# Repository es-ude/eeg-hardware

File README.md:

# 8-Channel EEG System

This repository contains the complete design and source files for a custom **8-Channel EEG System** (Electroencephalography) based on the Raspberry Pi Pico (RP2350A) and the Analog Devices AD7779 24-bit ADC.

The project is modular and covers the entire signal chain: from physical schematics and microcontroller firmware to data acquisition and visualization on the PC.

## Project Structure

The repository is organized into three main sections:

- **[`0_hardware/`](0_hardware/)**: KiCad projects for schematics and PCB layouts.
- **[`1_firmware/`](1_firmware/)**: C source code to be flashed onto the hardware.
- **[`2_pc_datahandler/`](2_pc_datahandler/)**: Python framework for control, data acquisition (LSL/HDF5), live plotting, and analysis.

---

## 0_Hardware

The hardware folder contains all electronic design files (KiCad).

**Key Components:**
*   **MCU:** Custom desgin based on the **RP2350A**.
*   **ADC:** [AD7779](https://www.analog.com/en/products/ad7779.html) (8-Channel, 24-Bit Sigma-Delta ADC).
*   **Signal Conditioning:** Variable gain settings via digital potentiometers (AD5142A).
*   **Modules:** Separate schematics for power management, impedance measurement, sensor interfaces, and active shielding reference.

---

## 1_Firmware

The firmware runs on the RP2350A and handles SPI communication with the ADC, I2C communication with digital potentiometers, and high-speed data transfer to the PC via USB.

**Features:**
*   **Sampling Rate:** Configurable sampling rate for the AD7779.
*   **Drivers:** Implemented for AD7779 (SPI), AD5142A (I2C), and GPIO shielding control.
*   **Protocol:** USB packet protocol with header/footer framing.
*   **Synchronization:** Microsecond-precision timestamping for every data packet.

**Build Instructions:**
Prerequisites: [Pico SDK](https://github.com/raspberrypi/pico-sdk) and CMake.

---

## 2_PC_DataHandler

This folder contains the Python-based host software to interface with the EEG hardware. It manages the USB connection, decodes the raw data stream, and integrates with the Lab Streaming Layer (LSL) ecosystem.

**Features:**
*   **Data Acquisition:** Reading from the USB serial port.
*   **LSL Integration:** Streams data as an 8-channel EEG signal onto the local network for use with tools like LabRecorder or our live plotter.
*   **Visualization:** Real-time plotting of time-series data.
*   **Analysis:** Signal quality verification.

**This project uses [`uv`](https://github.com/astral-sh/uv) for fast and reliable dependency management.**

Create a virtual environment and sync dependencies:
    ```bash
    uv sync
    ```

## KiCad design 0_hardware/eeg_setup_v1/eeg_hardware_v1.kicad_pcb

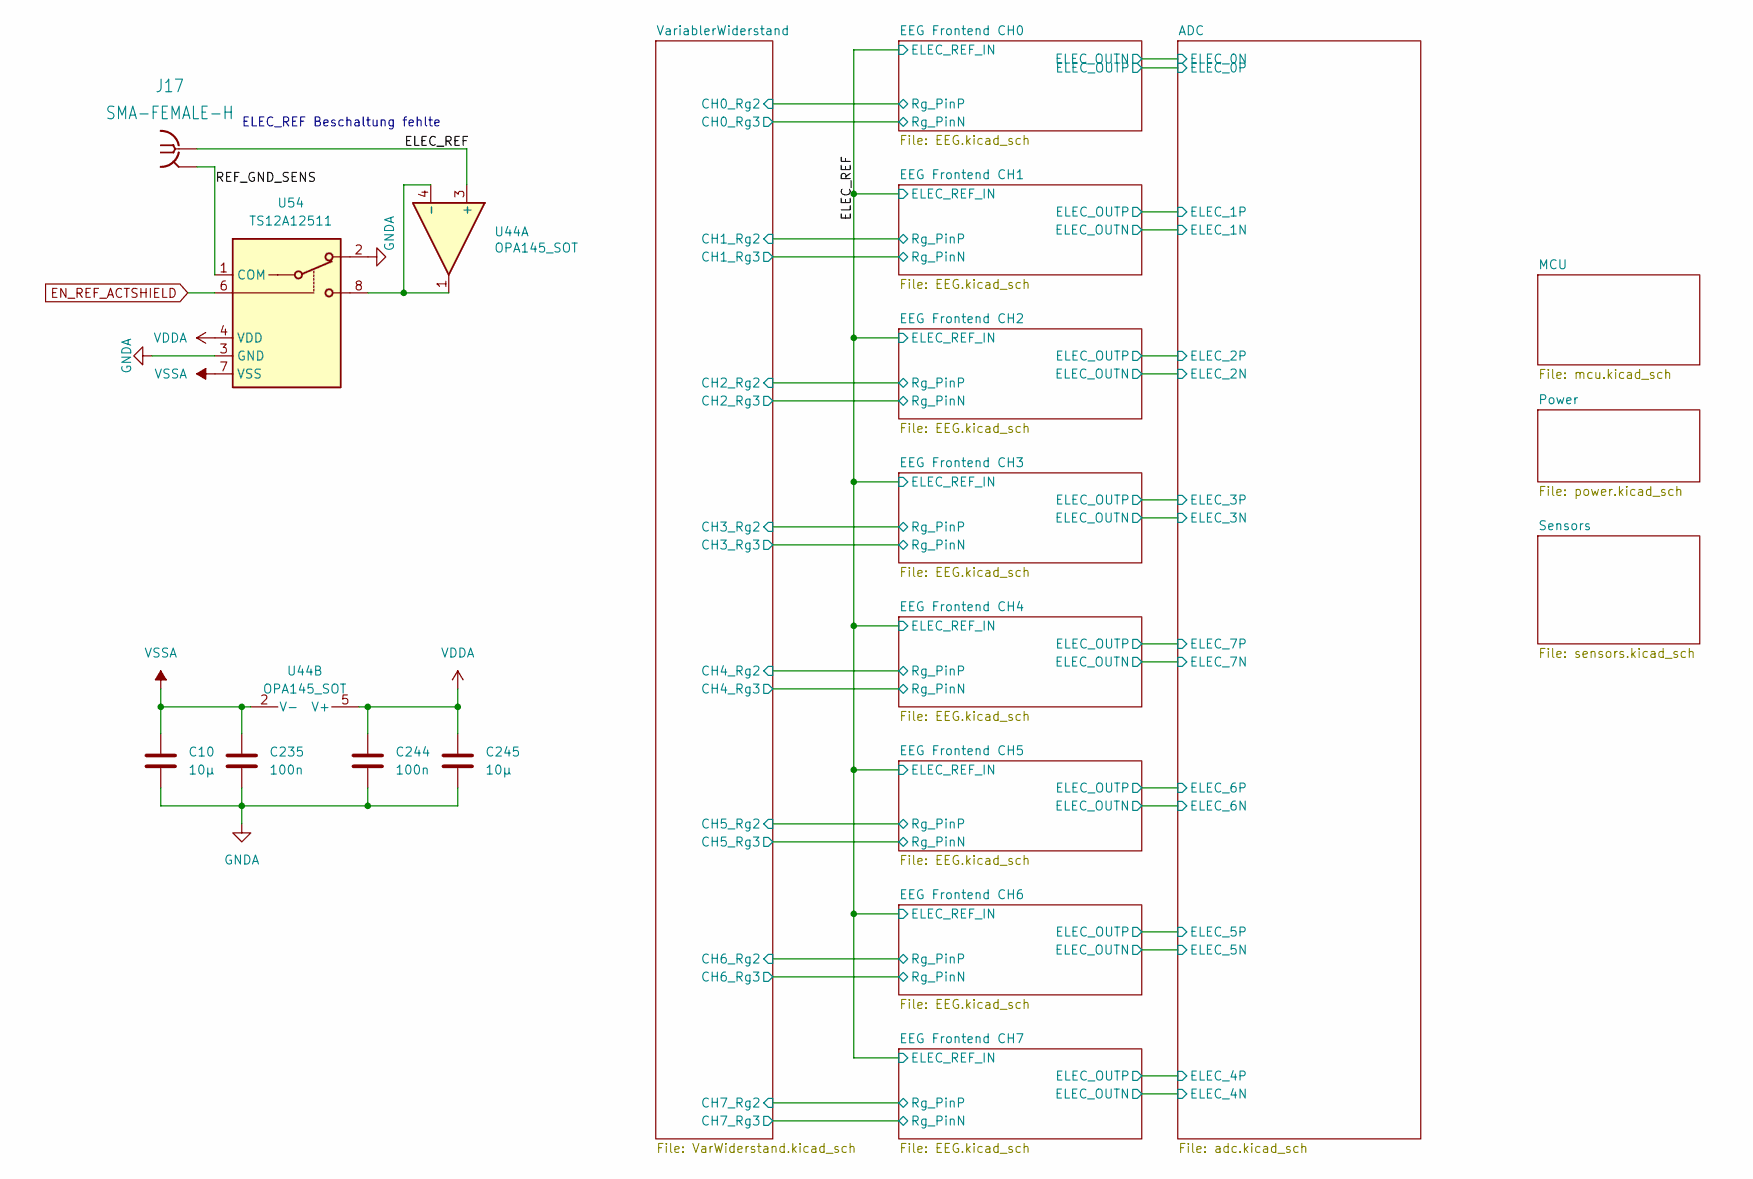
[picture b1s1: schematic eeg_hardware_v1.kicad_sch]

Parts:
C10, C245: 10µ; C_0603_1608Metric
C235, C244: 100n; C_0603_1608Metric
J17: SMA-FEMALE-H; SMA_Samtec_SMA-J-P-H-ST-EM1_EdgeMount
U44: OPA145_SOT; SOT-23-5_HandSoldering
U54: TS12A12511; SOT-23-8

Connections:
/ELEC_REF: J17.1 (SIG), U44.3 (+); also elsewhere on the board
/REF_GND_SENS: J17.2 (GND), U54.1 (COM)
EN_REF_ACTSHIELD: U54.6; also elsewhere on the board
GNDA: C10.2, C235.2, C244.2, C245.2, U54.2, U54.3 (GND); also elsewhere on the board
unnamed: U44.1, U44.4 (-), U54.8
VDDA: C244.1, C245.1, U44.5 (V+), U54.4 (VDD); also elsewhere on the board
VSSA: C10.1, C235.1, U44.2 (V-), U54.7 (VSS); also elsewhere on the board

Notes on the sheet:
ELEC_REF Beschaltung fehlte

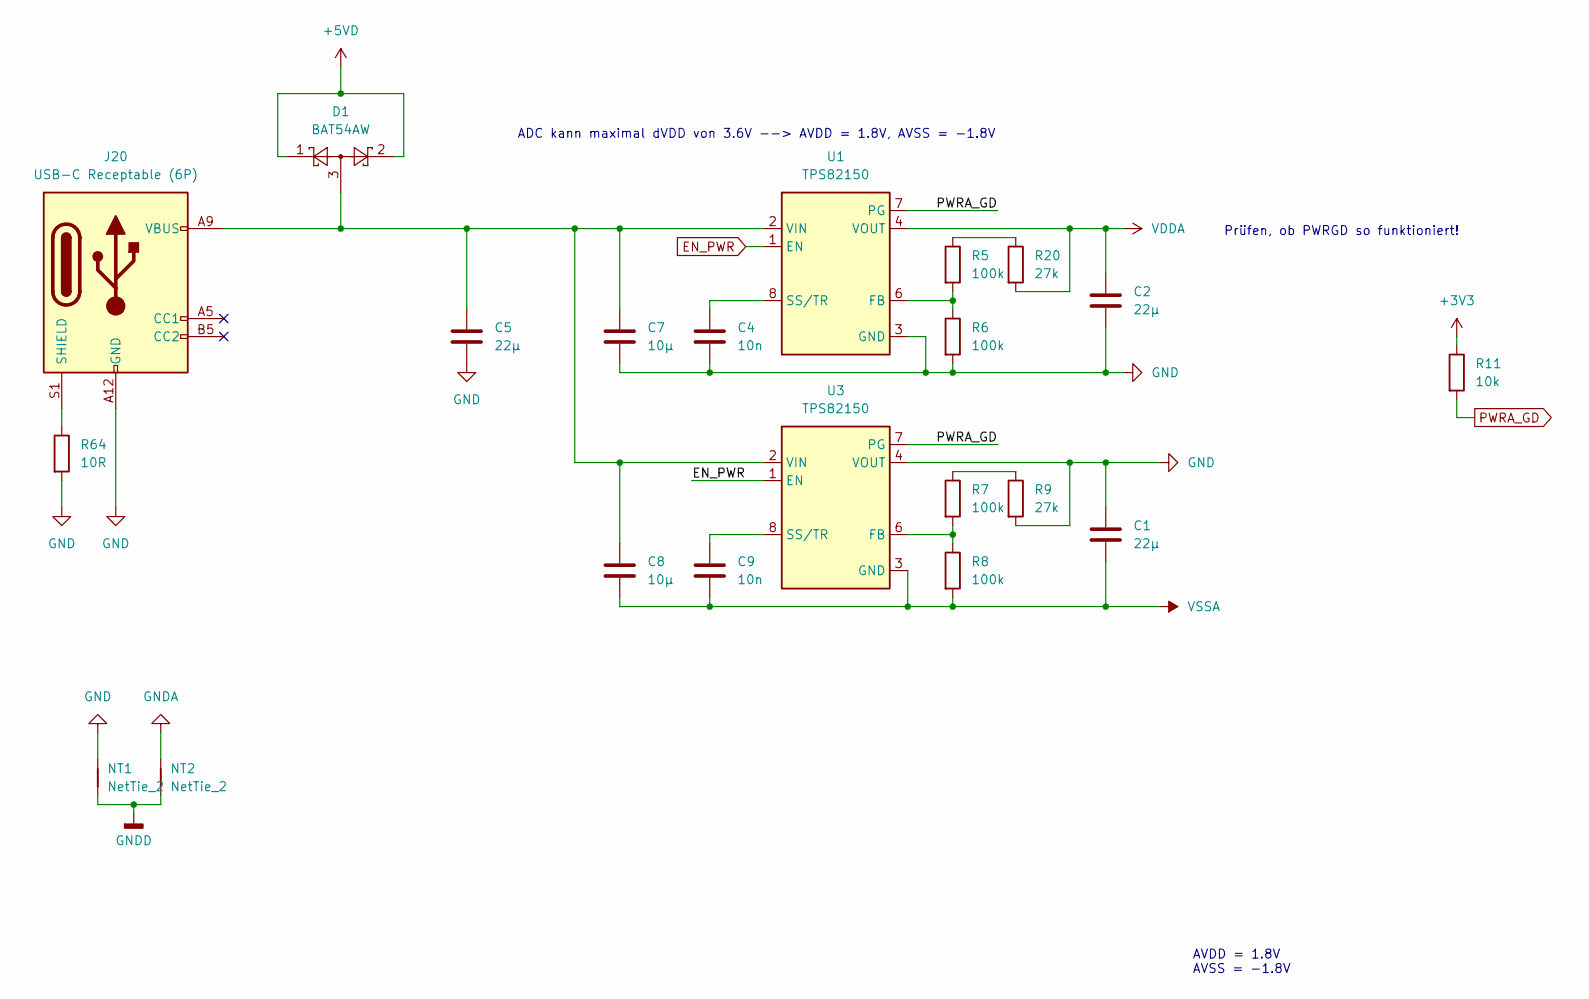
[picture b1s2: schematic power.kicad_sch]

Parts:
C1, C2, C5: 22µ; C_0805_2012Metric
C4, C9: 10n; C_0603_1608Metric
C7, C8: 10µ; C_0603_1608Metric
D1: BAT54AW; SOT-323_SC-70
J20: USB-C Receptable (6P); USB_C_Receptacle_6P
NT1, NT2: NetTie_2; NetTie-2_SMD_Pad2.0mm
R5, R6, R7, R8: 100k; R_0603_1608Metric
R9, R20: 27k; R_0603_1608Metric
R11: 10k; R_0603_1608Metric
R64: 10R; R_0603_1608Metric
U1, U3: TPS82150; Texas_SIL0008D_MicroSiP-8-1EP_2.8x3mm_P0.65mm_EP1.1x1.9mm

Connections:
+3V3: R11.1; also elsewhere on the board
+5VD: D1.1, D1.2; also elsewhere on the board
EN_PWR: U1.1 (EN), U3.1 (EN); also elsewhere on the board
GND: C1.1, C2.2, C4.2, C5.2, C7.2, J20.A12 (GND), J20.B12 (GND), NT1.2, R6.2, R9.2, R64.2, U1.3 (GND), U1.9 (GND), U3.4 (VOUT), U3.5 (VOUT)
GNDA: NT2.2; also elsewhere on the board
GNDD: NT1.1, NT2.1; also elsewhere on the board
unnamed: J20.S1 (SHIELD), R64.1
unnamed: R7.1, R9.1
unnamed: R5.1, R20.1
unnamed: R5.2, R6.1, U1.6 (FB)
unnamed: C4.1, U1.8 (SS/TR)
unnamed: C5.1, C7.1, C8.1, D1.3, J20.A9 (VBUS), J20.B9 (VBUS), U1.2 (VIN), U3.2 (VIN)
unnamed: R7.2, R8.1, U3.6 (FB)
unnamed: C9.1, U3.8 (SS/TR)
PWRA_GD: R11.2, U1.7 (PG), U3.7 (PG); also elsewhere on the board
VDDA: C2.1, R20.2, U1.4 (VOUT), U1.5 (VOUT); also elsewhere on the board
VSSA: C1.2, C8.2, C9.2, R8.2, U3.3 (GND), U3.9 (GND); also elsewhere on the board

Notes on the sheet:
AVDD = 1.8V AVSS = -1.8V
Prüfen, ob PWRGD so funktioniert!
ADC kann maximal dVDD von 3.6V --> AVDD = 1.8V, AVSS = -1.8V

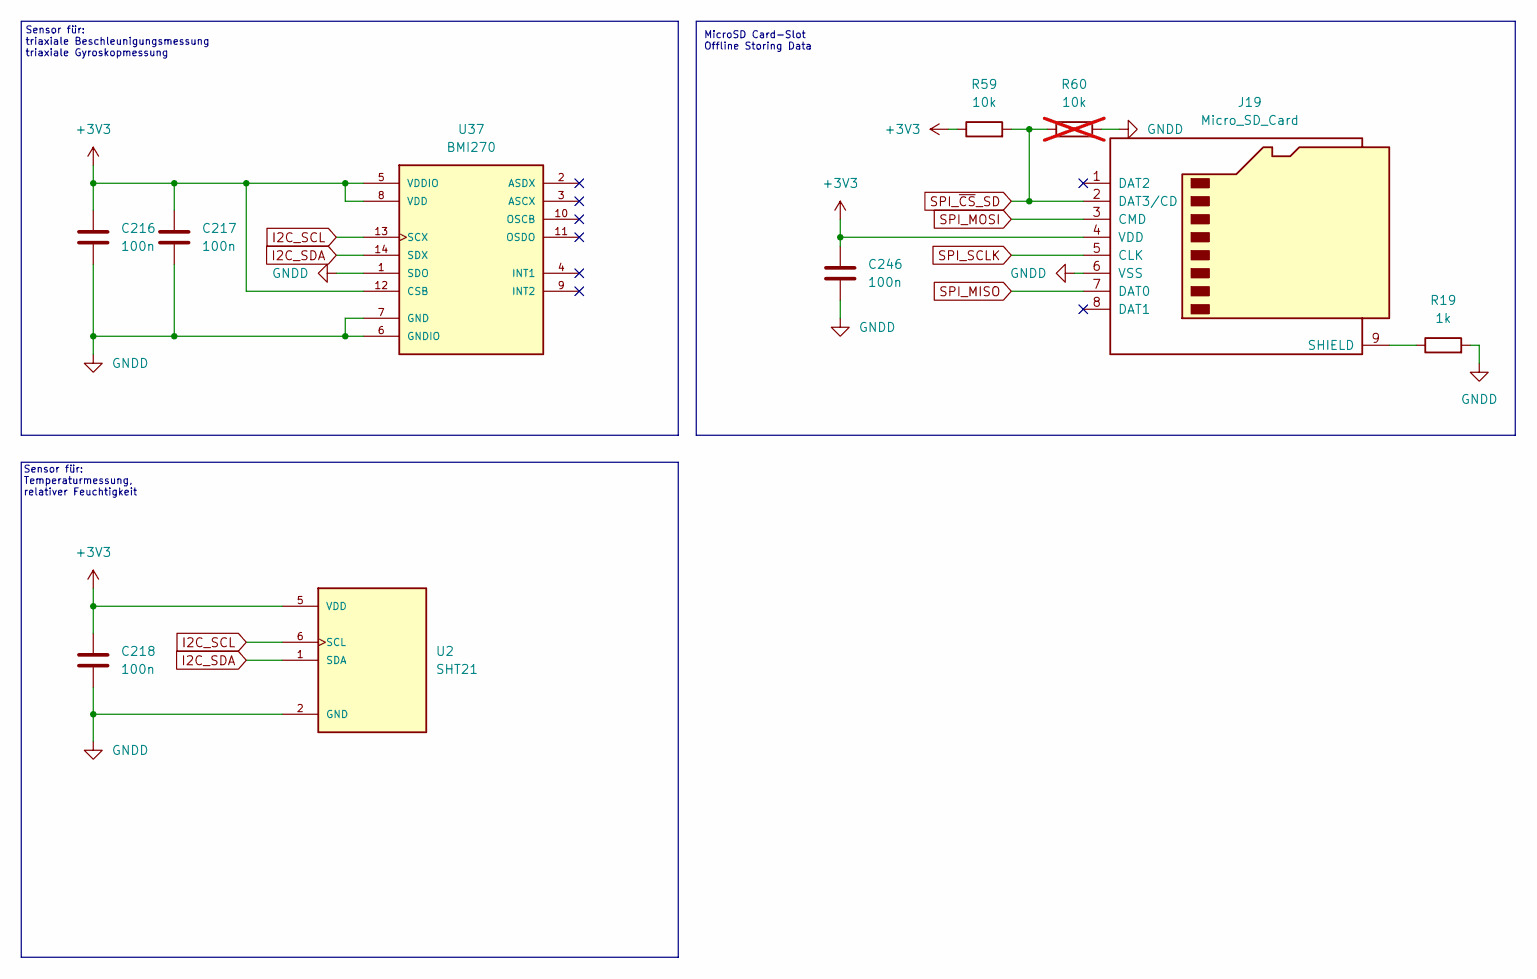
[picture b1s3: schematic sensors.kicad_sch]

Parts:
C216, C217, C218, C246: 100n; C_0603_1608Metric
J19: Micro_SD_Card; microSD_HC_Wuerth_693072010801
R19: 1k; R_0603_1608Metric
R59: 10k; R_0603_1608Metric
R60: 10k; R_0603_1608Metric; not fitted
U2: SHT21; XDCR_SHT21
U37: BMI270; XDCR_BMI270

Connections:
+3V3: C216.1, C217.1, C218.1, C246.1, J19.4 (VDD), R59.1, U2.5 (VDD), U37.5 (VDDIO), U37.8 (VDD), U37.12 (CSB); also elsewhere on the board
GNDD: C216.2, C217.2, C218.2, C246.2, J19.6 (VSS), R19.2, R60.2, U2.2 (GND), U2.7 (EXP), U37.1 (SDO), U37.6 (GNDIO), U37.7 (GND); also elsewhere on the board
I2C_SCL: U2.6 (SCL), U37.13 (SCX); also elsewhere on the board
I2C_SDA: U2.1 (SDA), U37.14 (SDX); also elsewhere on the board
unnamed: J19.9 (SHIELD), R19.1
SPI_MISO: J19.7 (DAT0); also elsewhere on the board
SPI_MOSI: J19.3 (CMD); also elsewhere on the board
SPI_SCLK: J19.5 (CLK); also elsewhere on the board
SPI_~CS_SD: J19.2 (DAT3/CD), R59.2, R60.1; also elsewhere on the board

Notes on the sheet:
MicroSD Card-Slot Offline Storing Data
Sensor für: Temperaturmessung, relativer Feuchtigkeit
Sensor für: triaxiale Beschleunigungsmessung triaxiale Gyroskopmessung

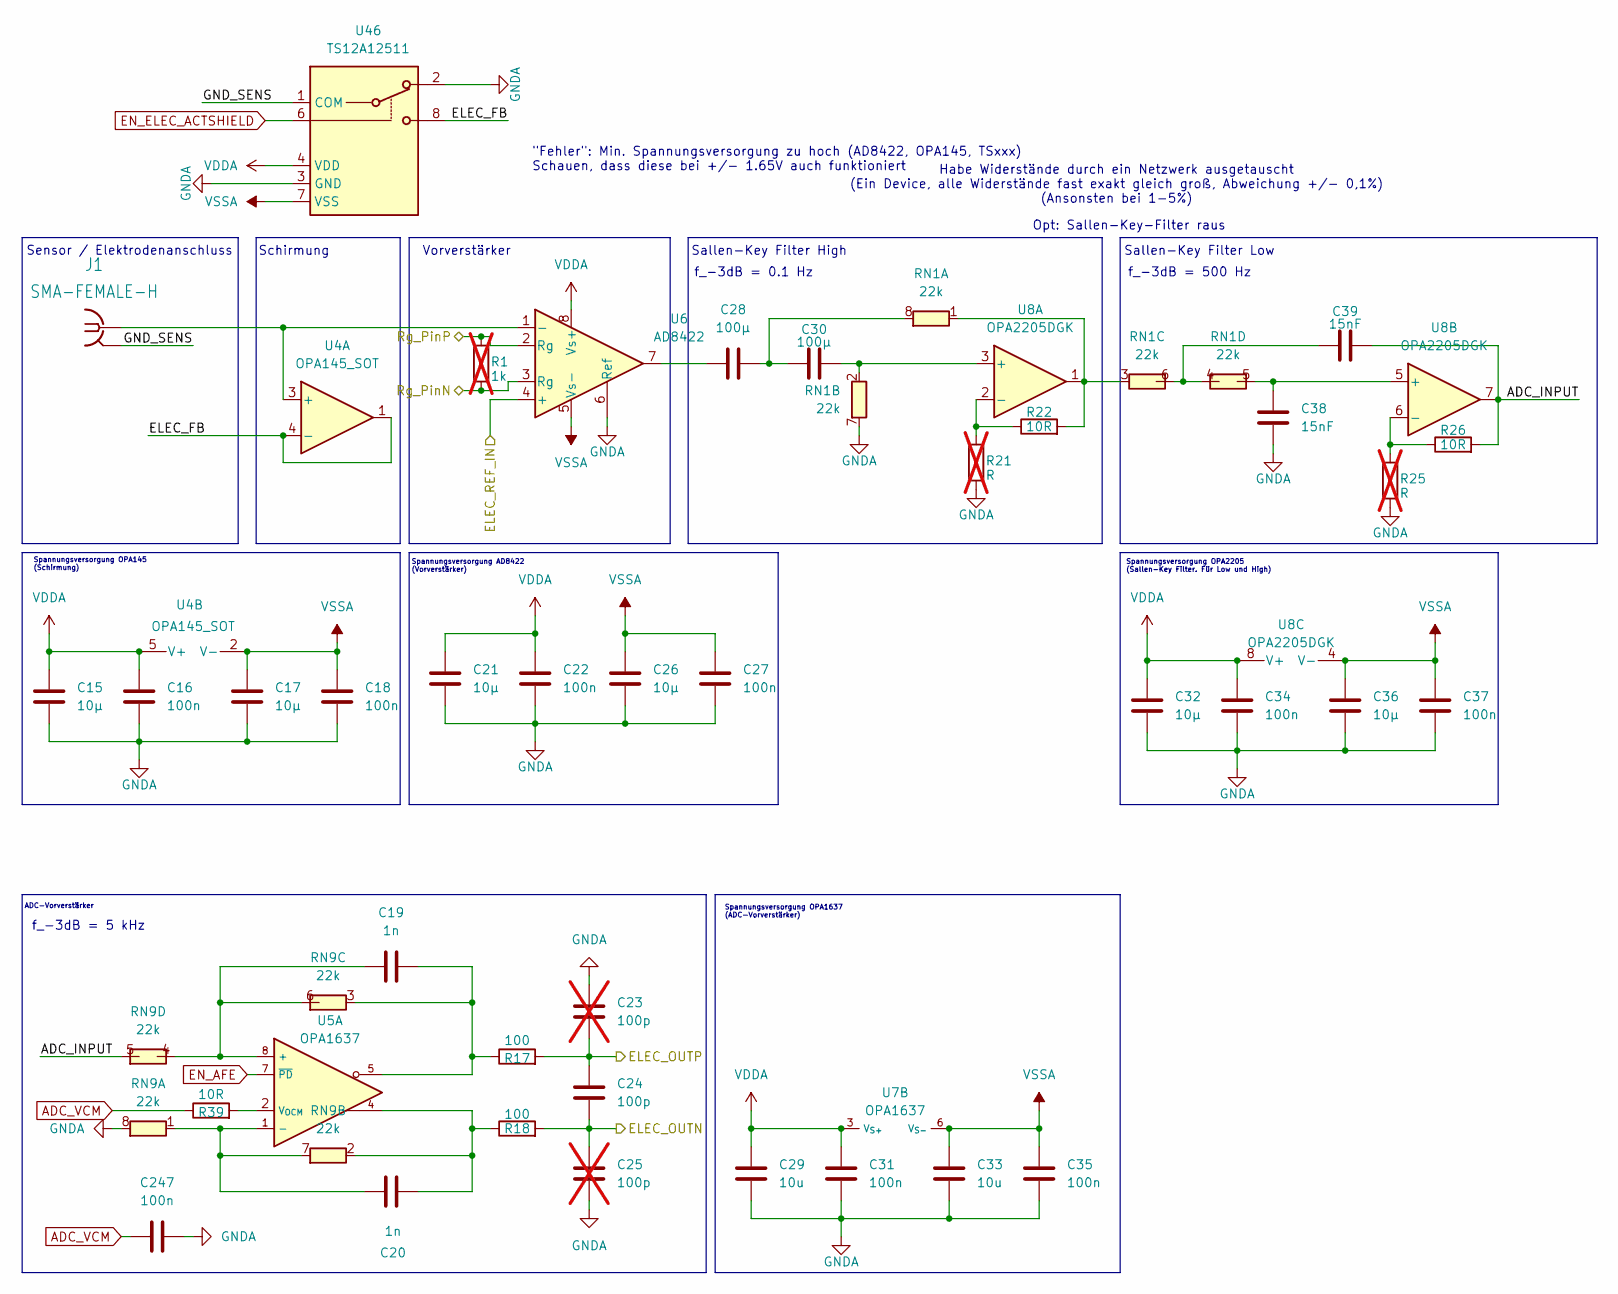
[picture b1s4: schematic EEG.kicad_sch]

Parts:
C15, C17, C21, C26, C32, C36: 10µ; C_0603_1608Metric
C16, C18, C22, C27, C31, C34, C35, C37, C247: 100n; C_0603_1608Metric
C19, C20: 1n; C_0603_1608Metric
C23, C25: 100p; C_0603_1608Metric; not fitted
C24: 100p; C_0603_1608Metric
C28, C30: 100µ; C_0603_1608Metric
C29, C33: 10u; C_0603_1608Metric
C38, C39: 15nF; C_0603_1608Metric
J1: SMA-FEMALE-H; SMA_Samtec_SMA-J-P-H-ST-EM1_EdgeMount
R1: 1k; R_0603_1608Metric; not fitted
R17, R18: 100; R_0603_1608Metric
R21, R25: R; R_0603_1608Metric; not fitted
R22, R26, R39: 10R; R_0603_1608Metric
RN1, RN9: 22k; RESCAXE80P320X160X70-8N
U4: OPA145_SOT; SOT-23-5_HandSoldering
U5, U7: OPA1637; VSSOP-8_3x3mm_P0.65mm
U6: AD8422; MSOP-8_3x3mm_P0.65mm
U8: OPA2205DGK; VSSOP-8_3x3mm_P0.65mm
U46: TS12A12511; SOT-23-8

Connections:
/ADC/ELEC_0N: C24.2, C25.1, R18.2; also elsewhere on the board
/ADC/ELEC_0P: C23.2, C24.1, R17.2; also elsewhere on the board
/EEG Frontend CH0/ADC_INPUT: C39.2, R26.2, RN9.5 (R4.2), U8.7
/EEG Frontend CH0/ELEC_FB: U4.1, U4.4 (-), U46.8
/EEG Frontend CH0/GND_SENS: J1.2 (GND), U46.1 (COM)
/EEG Frontend CH0/Rg_PinN: R1.1, U6.3 (Rg); also elsewhere on the board
/EEG Frontend CH0/Rg_PinP: R1.2, U6.2 (Rg); also elsewhere on the board
/ELEC_REF: U6.4 (+); also elsewhere on the board
ADC_VCM: C247.1, R39.1; also elsewhere on the board
EN_AFE: U5.7 (~PD), U7.7 (~PD); also elsewhere on the board
EN_ELEC_ACTSHIELD: U46.6; also elsewhere on the board
GNDA: C15.2, C16.2, C17.2, C18.2, C21.2, C22.2, C23.1, C25.2, C26.2, C27.2, C29.2, C31.2, C32.2, C33.2, C34.2, C35.2, C36.2, C37.2, C38.1, C247.2, R21.1, R25.1, RN1.7 (R2.2), RN9.8 (R1.2), U6.6 (Ref), U46.2, U46.3 (GND); also elsewhere on the board
unnamed: C28.2, U6.7
unnamed: J1.1 (SIG), U4.3 (+), U6.1 (-)
unnamed: R22.2, RN1.1 (R1.1), RN1.3 (R3.1), U8.1
unnamed: C28.1, C30.1, RN1.8 (R1.2)
unnamed: C30.2, RN1.2 (R2.1), U8.3 (+)
unnamed: C39.1, RN1.4 (R4.1), RN1.6 (R3.2)
unnamed: C38.2, RN1.5 (R4.2), U8.5 (+)
unnamed: C20.1, RN9.1 (R1.1), RN9.7 (R2.2), U5.1 (-)
unnamed: C20.2, R18.1, RN9.2 (R2.1), U5.4
unnamed: C19.2, R17.1, RN9.3 (R3.1), U5.5
unnamed: C19.1, RN9.4 (R4.1), RN9.6 (R3.2), U5.8 (+)
unnamed 157: U7.1 (-); also elsewhere on the board
unnamed 158: U7.4; also elsewhere on the board
unnamed 159: U7.5; also elsewhere on the board
unnamed 160: U7.8 (+); also elsewhere on the board
unnamed: R39.2, U5.2 (V_{OCM})
unnamed 183: U7.2 (V_{OCM}); also elsewhere on the board
unnamed: R21.2, R22.1, U8.2 (-)
unnamed: R25.2, R26.1, U8.6 (-)
VDDA: C15.1, C16.1, C21.1, C22.1, C29.1, C31.1, C32.1, C34.1, U4.5 (V+), U5.3 (V_{S+}), U6.8 (Vs+), U7.3 (V_{S+}), U8.8 (V+), U46.4 (VDD); also elsewhere on the board
VSSA: C17.1, C18.1, C26.1, C27.1, C33.1, C35.1, C36.1, C37.1, U4.2 (V-), U5.6 (V_{S-}), U6.5 (Vs-), U7.6 (V_{S-}), U8.4 (V-), U46.7 (VSS); also elsewhere on the board

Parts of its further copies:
C40, C42, C46, C51, C57, C61, C65, C67, C71, C76, C82, C86, C90, C92, C96, C101, C107, C111, C115, C117, C121, C126, C132, C136, C140, C142, C146, C151, C157, C161, C165, C167, C171, C176, C182, C186, C190, C192, C196, C201, C207, C211: 10µ; C_0603_1608Metric
C41, C43, C47, C52, C56, C59, C60, C62, C66, C68, C72, C77, C81, C84, C85, C87, C91, C93, C97, C102, C106, C109, C110, C112, C116, C118, C122, C127, C131, C134, C135, C137, C141, C143, C147, C152, C156, C159, C160, C162, C166, C168, C172, C177, C181, C184, C185, C187, C191, C193, C197, C202, C206, C209, C210, C212, C248, C249, C250, C251, C252, C253, C254: 100n; C_0603_1608Metric
C44, C45, C69, C70, C94, C95, C119, C120, C144, C145, C169, C170, C194, C195: 1n; C_0603_1608Metric
C48, C50, C73, C75, C98, C100, C123, C125, C148, C150, C173, C175, C198, C200: 100p; C_0603_1608Metric; not fitted
C49, C74, C99, C124, C149, C174, C199: 100p; C_0603_1608Metric
C53, C55, C78, C80, C103, C105, C128, C130, C153, C155, C178, C180, C203, C205: 100µ; C_0603_1608Metric
C54, C58, C79, C83, C104, C108, C129, C133, C154, C158, C179, C183, C204, C208: 10u; C_0603_1608Metric
C63, C64, C88, C89, C113, C114, C138, C139, C163, C164, C188, C189, C213, C214: 15nF; C_0603_1608Metric
J3, J5, J7, J9, J11, J13, J15: SMA-FEMALE-H; SMA_Samtec_SMA-J-P-H-ST-EM1_EdgeMount
R2, R3, R4, R12, R13, R14, R15: 1k; R_0603_1608Metric; not fitted
R32, R33, R47, R48, R62, R63, R77, R78, R92, R93, R107, R108, R122, R123: 100; R_0603_1608Metric
R36, R40, R51, R55, R66, R70, R81, R85, R96, R100, R111, R115, R126, R130: R; R_0603_1608Metric; not fitted
R37, R41, R42, R43, R44, R45, R49, R50, R52, R53, R56, R67, R71, R82, R86, R97, R101, R112, R116, R127, R131: 10R; R_0603_1608Metric
RN2, RN3, RN4, RN5, RN6, RN7, RN8, RN10, RN11, RN12, RN13, RN14, RN15, RN16: 22k; RESCAXE80P320X160X70-8N
U9, U14, U18, U22, U25, U29, U32: OPA145_SOT; SOT-23-5_HandSoldering
U10, U12, U15, U20, U27, U33: OPA1637; VSSOP-8_3x3mm_P0.65mm
U11, U16, U19, U23, U26, U30, U34: AD8422; MSOP-8_3x3mm_P0.65mm
U13, U17, U21, U24, U28, U31, U35: OPA2205DGK; VSSOP-8_3x3mm_P0.65mm
U47, U48, U49, U50, U51, U52, U53: TS12A12511; SOT-23-8

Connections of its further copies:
/ADC/ELEC_1N: C49.2, C50.1, R33.2; also elsewhere on the board
/ADC/ELEC_1P: C48.2, C49.1, R32.2; also elsewhere on the board
/ADC/ELEC_2N: C74.2, C75.1, R48.2; also elsewhere on the board
/ADC/ELEC_2P: C73.2, C74.1, R47.2; also elsewhere on the board
/ADC/ELEC_3N: C99.2, C100.1, R63.2; also elsewhere on the board
/ADC/ELEC_3P: C98.2, C99.1, R62.2; also elsewhere on the board
/ADC/ELEC_4N: C199.2, C200.1, R123.2; also elsewhere on the board
/ADC/ELEC_4P: C198.2, C199.1, R122.2; also elsewhere on the board
/ADC/ELEC_5N: C174.2, C175.1, R108.2; also elsewhere on the board
/ADC/ELEC_5P: C173.2, C174.1, R107.2; also elsewhere on the board
/ADC/ELEC_6N: C149.2, C150.1, R93.2; also elsewhere on the board
/ADC/ELEC_6P: C148.2, C149.1, R92.2; also elsewhere on the board
/ADC/ELEC_7N: C124.2, C125.1, R78.2; also elsewhere on the board
/ADC/ELEC_7P: C123.2, C124.1, R77.2; also elsewhere on the board
/EEG Frontend CH1/ADC_INPUT: C64.2, R41.2, RN10.5 (R4.2), U13.7
/EEG Frontend CH1/ELEC_FB: U9.1, U9.4 (-), U47.8
/EEG Frontend CH1/GND_SENS: J3.2 (GND), U47.1 (COM)
/EEG Frontend CH1/Rg_PinN: R2.1, U11.3 (Rg); also elsewhere on the board
/EEG Frontend CH1/Rg_PinP: R2.2, U11.2 (Rg); also elsewhere on the board
/EEG Frontend CH2/ADC_INPUT: C89.2, R56.2, RN11.5 (R4.2), U17.7
/EEG Frontend CH2/ELEC_FB: U14.1, U14.4 (-), U48.8
/EEG Frontend CH2/GND_SENS: J5.2 (GND), U48.1 (COM)
/EEG Frontend CH2/Rg_PinN: R3.1, U16.3 (Rg); also elsewhere on the board
/EEG Frontend CH2/Rg_PinP: R3.2, U16.2 (Rg); also elsewhere on the board
/EEG Frontend CH3/ADC_INPUT: C114.2, R71.2, RN12.5 (R4.2), U21.7
/EEG Frontend CH3/ELEC_FB: U18.1, U18.4 (-), U49.8
/EEG Frontend CH3/GND_SENS: J7.2 (GND), U49.1 (COM)
/EEG Frontend CH3/Rg_PinN: R4.1, U19.3 (Rg); also elsewhere on the board
/EEG Frontend CH3/Rg_PinP: R4.2, U19.2 (Rg); also elsewhere on the board
/EEG Frontend CH4/ADC_INPUT: C139.2, R86.2, RN13.5 (R4.2), U24.7
/EEG Frontend CH4/ELEC_FB: U22.1, U22.4 (-), U50.8
/EEG Frontend CH4/GND_SENS: J9.2 (GND), U50.1 (COM)
/EEG Frontend CH4/Rg_PinN: R12.1, U23.3 (Rg); also elsewhere on the board
/EEG Frontend CH4/Rg_PinP: R12.2, U23.2 (Rg); also elsewhere on the board
/EEG Frontend CH5/ADC_INPUT: C164.2, R101.2, RN14.5 (R4.2), U28.7
/EEG Frontend CH5/ELEC_FB: U25.1, U25.4 (-), U51.8
/EEG Frontend CH5/GND_SENS: J11.2 (GND), U51.1 (COM)
/EEG Frontend CH5/Rg_PinN: R13.1, U26.3 (Rg); also elsewhere on the board
/EEG Frontend CH5/Rg_PinP: R13.2, U26.2 (Rg); also elsewhere on the board
/EEG Frontend CH6/ADC_INPUT: C189.2, R116.2, RN15.5 (R4.2), U31.7
/EEG Frontend CH6/ELEC_FB: U29.1, U29.4 (-), U52.8
/EEG Frontend CH6/GND_SENS: J13.2 (GND), U52.1 (COM)
/EEG Frontend CH6/Rg_PinN: R14.1, U30.3 (Rg); also elsewhere on the board
/EEG Frontend CH6/Rg_PinP: R14.2, U30.2 (Rg); also elsewhere on the board
/EEG Frontend CH7/ADC_INPUT: C214.2, R131.2, RN16.5 (R4.2), U35.7
/EEG Frontend CH7/ELEC_FB: U32.1, U32.4 (-), U53.8
/EEG Frontend CH7/GND_SENS: J15.2 (GND), U53.1 (COM)
/EEG Frontend CH7/Rg_PinN: R15.1, U34.3 (Rg); also elsewhere on the board
/EEG Frontend CH7/Rg_PinP: R15.2, U34.2 (Rg); also elsewhere on the board
/ELEC_REF: U11.4 (+), U16.4 (+), U19.4 (+), U23.4 (+), U26.4 (+), U30.4 (+), U34.4 (+); also elsewhere on the board
ADC_VCM: C248.1, C249.1, C250.1, C251.1, C252.1, C253.1, C254.1, R42.1, R43.1, R44.1, R45.1, R49.1, R50.1, R53.1; also elsewhere on the board
EN_AFE: U10.7 (~PD), U12.7 (~PD), U15.7 (~PD), U20.7 (~PD), U27.7 (~PD), U33.7 (~PD); also elsewhere on the board
EN_ELEC_ACTSHIELD: U47.6, U48.6, U49.6, U50.6, U51.6, U52.6, U53.6; also elsewhere on the board
GNDA: C40.2, C41.2, C42.2, C43.2, C46.2, C47.2, C48.1, C50.2, C51.2, C52.2, C54.2, C56.2, C57.2, C58.2, C59.2, C60.2, C61.2, C62.2, C63.1, C65.2, C66.2, C67.2, C68.2, C71.2, C72.2, C73.1, C75.2, C76.2, C77.2, C79.2, C81.2, C82.2, C83.2, C84.2, C85.2, C86.2, C87.2, C88.1, C90.2, C91.2, C92.2, C93.2, C96.2, C97.2, C98.1, C100.2, C101.2, C102.2, C104.2, C106.2, C107.2, C108.2, C109.2, C110.2, C111.2, C112.2, C113.1, C115.2, C116.2, C117.2, C118.2, C121.2, C122.2, C123.1, C125.2, C126.2, C127.2, C129.2, C131.2, C132.2, C133.2, C134.2, C135.2, C136.2, C137.2, C138.1, C140.2, C141.2, C142.2, C143.2, C146.2, C147.2, C148.1, C150.2, C151.2, C152.2, C154.2, C156.2, C157.2, C158.2, C159.2, C160.2, C161.2, C162.2, C163.1, C165.2, C166.2, C167.2, C168.2, C171.2, C172.2, C173.1, C175.2, C176.2, C177.2, C179.2, C181.2, C182.2, C183.2, C184.2, C185.2, C186.2, C187.2, C188.1, C190.2, C191.2, C192.2, C193.2, C196.2, C197.2, C198.1, C200.2, C201.2, C202.2, C204.2, C206.2, C207.2, C208.2, C209.2, C210.2, C211.2, C212.2, C213.1, C248.2, C249.2, C250.2, C251.2, C252.2, C253.2, C254.2, R36.1, R40.1, R51.1, R55.1, R66.1, R70.1, R81.1, R85.1, R96.1, R100.1, R111.1, R115.1, R126.1, R130.1, RN2.7 (R2.2), RN3.7 (R2.2), RN4.7 (R2.2), RN5.7 (R2.2), RN6.7 (R2.2), RN7.7 (R2.2), RN8.7 (R2.2), RN10.8 (R1.2), RN11.8 (R1.2), RN12.8 (R1.2), RN13.8 (R1.2), RN14.8 (R1.2), RN15.8 (R1.2), RN16.8 (R1.2), U11.6 (Ref), U16.6 (Ref), U19.6 (Ref), U23.6 (Ref), U26.6 (Ref), U30.6 (Ref), U34.6 (Ref), U47.2, U47.3 (GND), U48.2, U48.3 (GND), U49.2, U49.3 (GND), U50.2, U50.3 (GND), U51.2, U51.3 (GND), U52.2, U52.3 (GND), U53.2, U53.3 (GND); also elsewhere on the board
unnamed: C53.2, U11.7
unnamed: C78.2, U16.7
unnamed: C103.2, U19.7
unnamed: C128.2, U23.7
unnamed: C153.2, U26.7
unnamed: C178.2, U30.7
unnamed: C203.2, U34.7
unnamed: J3.1 (SIG), U9.3 (+), U11.1 (-)
unnamed: J5.1 (SIG), U14.3 (+), U16.1 (-)
unnamed: J7.1 (SIG), U18.3 (+), U19.1 (-)
unnamed: J9.1 (SIG), U22.3 (+), U23.1 (-)
unnamed: J11.1 (SIG), U25.3 (+), U26.1 (-)
unnamed: J13.1 (SIG), U29.3 (+), U30.1 (-)
unnamed: J15.1 (SIG), U32.3 (+), U34.1 (-)
unnamed: R37.2, RN2.1 (R1.1), RN2.3 (R3.1), U13.1
unnamed: C53.1, C55.1, RN2.8 (R1.2)
unnamed: C55.2, RN2.2 (R2.1), U13.3 (+)
unnamed: C64.1, RN2.4 (R4.1), RN2.6 (R3.2)
unnamed: C63.2, RN2.5 (R4.2), U13.5 (+)
unnamed: R52.2, RN3.1 (R1.1), RN3.3 (R3.1), U17.1
unnamed: C78.1, C80.1, RN3.8 (R1.2)
unnamed: C80.2, RN3.2 (R2.1), U17.3 (+)
unnamed: C89.1, RN3.4 (R4.1), RN3.6 (R3.2)
unnamed: C88.2, RN3.5 (R4.2), U17.5 (+)
unnamed: R67.2, RN4.1 (R1.1), RN4.3 (R3.1), U21.1
unnamed: C103.1, C105.1, RN4.8 (R1.2)
unnamed: C105.2, RN4.2 (R2.1), U21.3 (+)
unnamed: C114.1, RN4.4 (R4.1), RN4.6 (R3.2)
unnamed: C113.2, RN4.5 (R4.2), U21.5 (+)
unnamed: R82.2, RN5.1 (R1.1), RN5.3 (R3.1), U24.1
unnamed: C128.1, C130.1, RN5.8 (R1.2)
unnamed: C130.2, RN5.2 (R2.1), U24.3 (+)
unnamed: C139.1, RN5.4 (R4.1), RN5.6 (R3.2)
unnamed: C138.2, RN5.5 (R4.2), U24.5 (+)
unnamed: R97.2, RN6.1 (R1.1), RN6.3 (R3.1), U28.1
unnamed: C153.1, C155.1, RN6.8 (R1.2)
unnamed: C155.2, RN6.2 (R2.1), U28.3 (+)
unnamed: C164.1, RN6.4 (R4.1), RN6.6 (R3.2)
unnamed: C163.2, RN6.5 (R4.2), U28.5 (+)
unnamed: R112.2, RN7.1 (R1.1), RN7.3 (R3.1), U31.1
unnamed: C178.1, C180.1, RN7.8 (R1.2)
unnamed: C180.2, RN7.2 (R2.1), U31.3 (+)
unnamed: C189.1, RN7.4 (R4.1), RN7.6 (R3.2)
unnamed: C188.2, RN7.5 (R4.2), U31.5 (+)
unnamed: R127.2, RN8.1 (R1.1), RN8.3 (R3.1), U35.1
unnamed: C203.1, C205.1, RN8.8 (R1.2)
unnamed: C205.2, RN8.2 (R2.1), U35.3 (+)
unnamed: C214.1, RN8.4 (R4.1), RN8.6 (R3.2)
unnamed: C213.2, RN8.5 (R4.2), U35.5 (+)
unnamed: C45.1, RN10.1 (R1.1), RN10.7 (R2.2), U10.1 (-)
unnamed: C45.2, R33.1, RN10.2 (R2.1), U10.4
unnamed: C44.2, R32.1, RN10.3 (R3.1), U10.5
unnamed: C44.1, RN10.4 (R4.1), RN10.6 (R3.2), U10.8 (+)
unnamed: C70.1, RN11.1 (R1.1), RN11.7 (R2.2), U15.1 (-)
unnamed: C70.2, R48.1, RN11.2 (R2.1), U15.4
unnamed: C69.2, R47.1, RN11.3 (R3.1), U15.5
unnamed: C69.1, RN11.4 (R4.1), RN11.6 (R3.2), U15.8 (+)
unnamed 157: C95.1, RN12.1 (R1.1), RN12.7 (R2.2); also elsewhere on the board
unnamed 158: C95.2, R63.1, RN12.2 (R2.1); also elsewhere on the board
unnamed 159: C94.2, R62.1, RN12.3 (R3.1); also elsewhere on the board
unnamed 160: C94.1, RN12.4 (R4.1), RN12.6 (R3.2); also elsewhere on the board
unnamed: C120.1, RN13.1 (R1.1), RN13.7 (R2.2), U12.1 (-)
unnamed: C120.2, R78.1, RN13.2 (R2.1), U12.4
unnamed: C119.2, R77.1, RN13.3 (R3.1), U12.5
unnamed: C119.1, RN13.4 (R4.1), RN13.6 (R3.2), U12.8 (+)
unnamed: C145.1, RN14.1 (R1.1), RN14.7 (R2.2), U20.1 (-)
unnamed: C145.2, R93.1, RN14.2 (R2.1), U20.4
unnamed: C144.2, R92.1, RN14.3 (R3.1), U20.5
unnamed: C144.1, RN14.4 (R4.1), RN14.6 (R3.2), U20.8 (+)
unnamed: C170.1, RN15.1 (R1.1), RN15.7 (R2.2), U27.1 (-)
unnamed: C170.2, R108.1, RN15.2 (R2.1), U27.4
unnamed: C169.2, R107.1, RN15.3 (R3.1), U27.5
unnamed: C169.1, RN15.4 (R4.1), RN15.6 (R3.2), U27.8 (+)
unnamed: C195.1, RN16.1 (R1.1), RN16.7 (R2.2), U33.1 (-)
unnamed: C195.2, R123.1, RN16.2 (R2.1), U33.4
unnamed: C194.2, R122.1, RN16.3 (R3.1), U33.5
unnamed: C194.1, RN16.4 (R4.1), RN16.6 (R3.2), U33.8 (+)
unnamed 183: R44.2; also elsewhere on the board
unnamed: R42.2, U10.2 (V_{OCM})
unnamed: R45.2, U12.2 (V_{OCM})
unnamed: R36.2, R37.1, U13.2 (-)
unnamed: R40.2, R41.1, U13.6 (-)
unnamed: R43.2, U15.2 (V_{OCM})
unnamed: R51.2, R52.1, U17.2 (-)
unnamed: R55.2, R56.1, U17.6 (-)
unnamed: R49.2, U20.2 (V_{OCM})
unnamed: R66.2, R67.1, U21.2 (-)
unnamed: R70.2, R71.1, U21.6 (-)
unnamed: R81.2, R82.1, U24.2 (-)
unnamed: R85.2, R86.1, U24.6 (-)
unnamed: R50.2, U27.2 (V_{OCM})
unnamed: R96.2, R97.1, U28.2 (-)
unnamed: R100.2, R101.1, U28.6 (-)
unnamed: R111.2, R112.1, U31.2 (-)
unnamed: R115.2, R116.1, U31.6 (-)
unnamed: R53.2, U33.2 (V_{OCM})
unnamed: R126.2, R127.1, U35.2 (-)
unnamed: R130.2, R131.1, U35.6 (-)
VDDA: C40.1, C41.1, C46.1, C47.1, C54.1, C56.1, C57.1, C59.1, C65.1, C66.1, C71.1, C72.1, C79.1, C81.1, C82.1, C84.1, C90.1, C91.1, C96.1, C97.1, C104.1, C106.1, C107.1, C109.1, C115.1, C116.1, C121.1, C122.1, C129.1, C131.1, C132.1, C134.1, C140.1, C141.1, C146.1, C147.1, C154.1, C156.1, C157.1, C159.1, C165.1, C166.1, C171.1, C172.1, C179.1, C181.1, C182.1, C184.1, C190.1, C191.1, C196.1, C197.1, C204.1, C206.1, C207.1, C209.1, U9.5 (V+), U10.3 (V_{S+}), U11.8 (Vs+), U12.3 (V_{S+}), U13.8 (V+), U14.5 (V+), U15.3 (V_{S+}), U16.8 (Vs+), U17.8 (V+), U18.5 (V+), U19.8 (Vs+), U20.3 (V_{S+}), U21.8 (V+), U22.5 (V+), U23.8 (Vs+), U24.8 (V+), U25.5 (V+), U26.8 (Vs+), U27.3 (V_{S+}), U28.8 (V+), U29.5 (V+), U30.8 (Vs+), U31.8 (V+), U32.5 (V+), U33.3 (V_{S+}), U34.8 (Vs+), U35.8 (V+), U47.4 (VDD), U48.4 (VDD), U49.4 (VDD), U50.4 (VDD), U51.4 (VDD), U52.4 (VDD), U53.4 (VDD); also elsewhere on the board
VSSA: C42.1, C43.1, C51.1, C52.1, C58.1, C60.1, C61.1, C62.1, C67.1, C68.1, C76.1, C77.1, C83.1, C85.1, C86.1, C87.1, C92.1, C93.1, C101.1, C102.1, C108.1, C110.1, C111.1, C112.1, C117.1, C118.1, C126.1, C127.1, C133.1, C135.1, C136.1, C137.1, C142.1, C143.1, C151.1, C152.1, C158.1, C160.1, C161.1, C162.1, C167.1, C168.1, C176.1, C177.1, C183.1, C185.1, C186.1, C187.1, C192.1, C193.1, C201.1, C202.1, C208.1, C210.1, C211.1, C212.1, U9.2 (V-), U10.6 (V_{S-}), U11.5 (Vs-), U12.6 (V_{S-}), U13.4 (V-), U14.2 (V-), U15.6 (V_{S-}), U16.5 (Vs-), U17.4 (V-), U18.2 (V-), U19.5 (Vs-), U20.6 (V_{S-}), U21.4 (V-), U22.2 (V-), U23.5 (Vs-), U24.4 (V-), U25.2 (V-), U26.5 (Vs-), U27.6 (V_{S-}), U28.4 (V-), U29.2 (V-), U30.5 (Vs-), U31.4 (V-), U32.2 (V-), U33.6 (V_{S-}), U34.5 (Vs-), U35.4 (V-), U47.7 (VSS), U48.7 (VSS), U49.7 (VSS), U50.7 (VSS), U51.7 (VSS), U52.7 (VSS), U53.7 (VSS); also elsewhere on the board

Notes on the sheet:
Spannungsversorgung AD8422 (Vorverstärker)
Opt: Sallen-Key-Filter raus
f_-3dB = 0.1 Hz
Sallen-Key Filter Low
Schirmung
Vorverstärker
Spannungsversorgung OPA1637 (ADC-Vorverstärker)
"Fehler": Min. Spannungsversorgung zu hoch (AD8422, OPA145, TSxxx) Schauen, dass diese bei +/- 1.65V auch funktioniert
Spannungsversorgung OPA145 (Schirmung)
ADC-Vorverstärker
Sensor / Elektrodenanschluss
Habe Widerstände durch ein Netzwerk ausgetauscht (Ein Device, alle Widerstände fast exakt gleich groß, Abweichung +/- 0,1%) (Ansonsten bei 1-5%)
f_-3dB = 500 Hz
Spannungsversorgung OPA2205 (Sallen-Key Filter. Für Low und High)
f_-3dB = 5 kHz
Sallen-Key Filter High

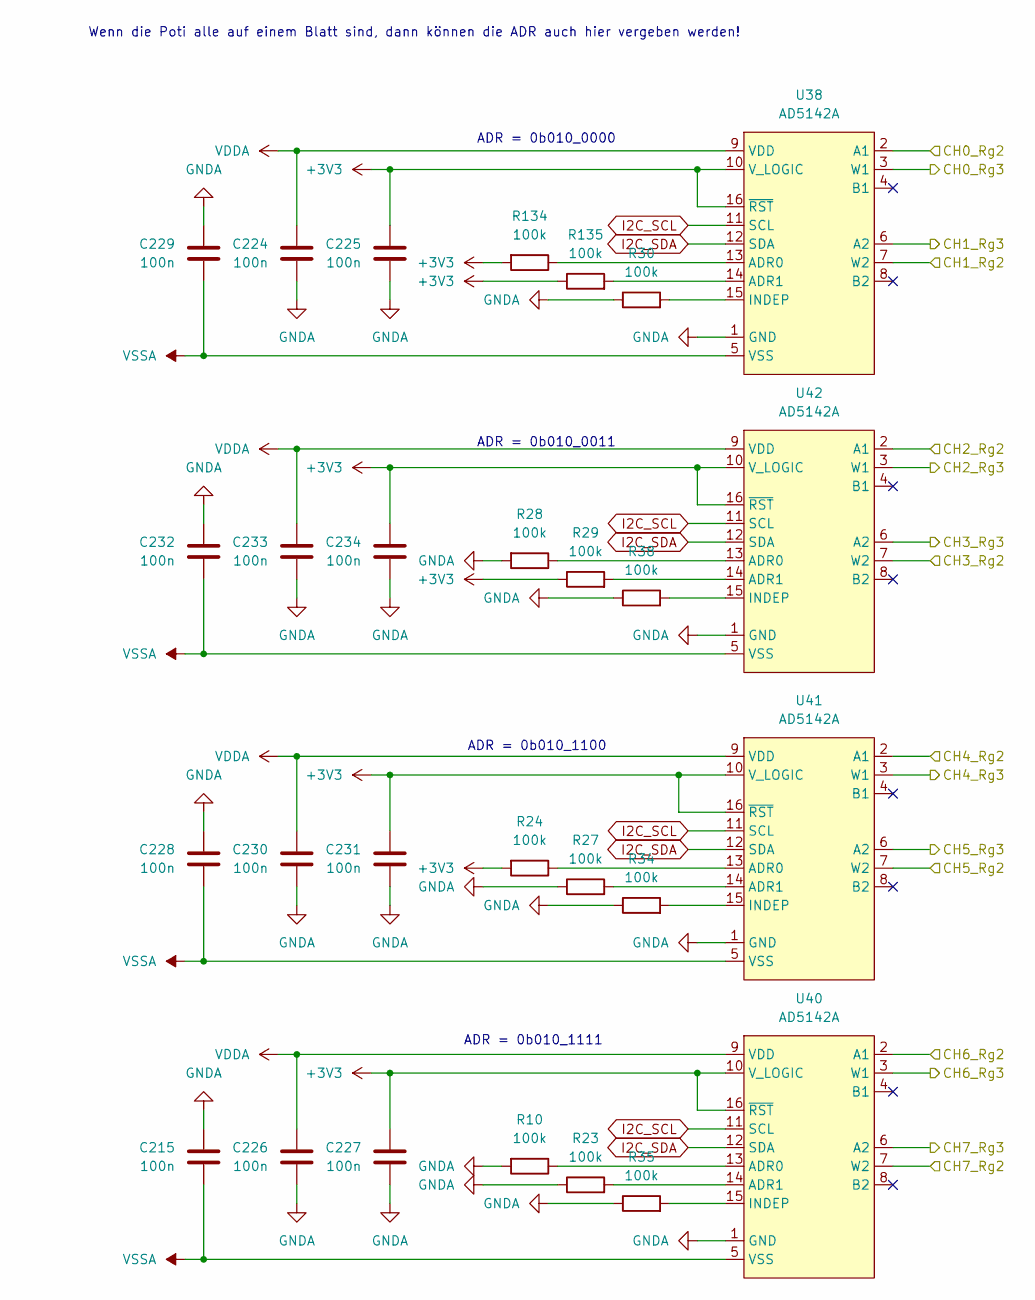
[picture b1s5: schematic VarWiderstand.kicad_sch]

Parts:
C215, C224, C225, C226, C227, C228, C229, C230, C231, C232, C233, C234: 100n; C_0603_1608Metric
R10, R23, R24, R27, R28, R29, R30, R34, R35, R38, R134, R135: 100k; R_0603_1608Metric
U38, U40, U41, U42: AD5142A; LFCSP-16-1EP_3x3mm_P0.5mm_EP1.5x1.5mm

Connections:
+3V3: C225.1, C227.1, C231.1, C234.1, R24.2, R29.1, R134.2, R135.1, U38.10 (V_LOGIC), U38.16 (~RST), U40.10 (V_LOGIC), U40.16 (~RST), U41.10 (V_LOGIC), U41.16 (~RST), U42.10 (V_LOGIC), U42.16 (~RST); also elsewhere on the board
/EEG Frontend CH0/Rg_PinN: U38.3 (W1); also elsewhere on the board
/EEG Frontend CH0/Rg_PinP: U38.2 (A1); also elsewhere on the board
/EEG Frontend CH1/Rg_PinN: U38.6 (A2); also elsewhere on the board
/EEG Frontend CH1/Rg_PinP: U38.7 (W2); also elsewhere on the board
/EEG Frontend CH2/Rg_PinN: U42.3 (W1); also elsewhere on the board
/EEG Frontend CH2/Rg_PinP: U42.2 (A1); also elsewhere on the board
/EEG Frontend CH3/Rg_PinN: U42.6 (A2); also elsewhere on the board
/EEG Frontend CH3/Rg_PinP: U42.7 (W2); also elsewhere on the board
/EEG Frontend CH4/Rg_PinN: U41.3 (W1); also elsewhere on the board
/EEG Frontend CH4/Rg_PinP: U41.2 (A1); also elsewhere on the board
/EEG Frontend CH5/Rg_PinN: U41.6 (A2); also elsewhere on the board
/EEG Frontend CH5/Rg_PinP: U41.7 (W2); also elsewhere on the board
/EEG Frontend CH6/Rg_PinN: U40.3 (W1); also elsewhere on the board
/EEG Frontend CH6/Rg_PinP: U40.2 (A1); also elsewhere on the board
/EEG Frontend CH7/Rg_PinN: U40.6 (A2); also elsewhere on the board
/EEG Frontend CH7/Rg_PinP: U40.7 (W2); also elsewhere on the board
GNDA: C215.1, C224.2, C225.2, C226.2, C227.2, C228.1, C229.1, C230.2, C231.2, C232.1, C233.2, C234.2, R10.2, R23.1, R27.1, R28.2, R30.1, R34.1, R35.1, R38.1, U38.1 (GND), U40.1 (GND), U41.1 (GND), U42.1 (GND); also elsewhere on the board
I2C_SCL: U38.11 (SCL), U40.11 (SCL), U41.11 (SCL), U42.11 (SCL); also elsewhere on the board
I2C_SDA: U38.12 (SDA), U40.12 (SDA), U41.12 (SDA), U42.12 (SDA); also elsewhere on the board
unnamed: R134.1, U38.13 (ADR0)
unnamed: R135.2, U38.14 (ADR1)
unnamed: R30.2, U38.15 (INDEP)
unnamed: R10.1, U40.13 (ADR0)
unnamed: R23.2, U40.14 (ADR1)
unnamed: R35.2, U40.15 (INDEP)
unnamed: R24.1, U41.13 (ADR0)
unnamed: R27.2, U41.14 (ADR1)
unnamed: R34.2, U41.15 (INDEP)
unnamed: R28.1, U42.13 (ADR0)
unnamed: R29.2, U42.14 (ADR1)
unnamed: R38.2, U42.15 (INDEP)
VDDA: C224.1, C226.1, C230.1, C233.1, U38.9 (VDD), U40.9 (VDD), U41.9 (VDD), U42.9 (VDD); also elsewhere on the board
VSSA: C215.2, C228.2, C229.2, C232.2, U38.5 (VSS), U38.17 (EXP), U40.5 (VSS), U40.17 (EXP), U41.5 (VSS), U41.17 (EXP), U42.5 (VSS), U42.17 (EXP); also elsewhere on the board

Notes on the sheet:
ADR = 0b010_0000
Wenn die Poti alle auf einem Blatt sind, dann können die ADR auch hier vergeben werden!
ADR = 0b010_1111
ADR = 0b010_0011
ADR = 0b010_1100

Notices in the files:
0_hardware/eeg_setup_v1/eeg_hardware_v1.kicad_pcb:
1v0 (c) 2025
0_hardware/eeg_setup_v2/eeg_hardware_v1.kicad_pcb:
2v0 (c) 2025
parts and their libraries:
License: Apache-2.0
